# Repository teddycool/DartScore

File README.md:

# DartScore

DartScore is an open-source experiment in detecting darts with cameras and turning board hits into game scores. The repository contains a historical Python 3 single-camera MVP and a new, documented direction for a two-Pi system.

## Project status

- **Available now:** the original one-camera Pygame prototype, recorded test videos, a simple-score GameService, a durable camera-free simulator, an HTTP/SSE engine API, a web scoreboard/proxy, and optional boot-starting user services for the two Pis.
- **In design:** two-camera capture on a Raspberry Pi 5, 301/501 rules, browser kiosk startup, and status LEDs.
- **Accuracy:** the legacy detector is experimental. Replay candidate counts are a reproducible software baseline, not verified scoring accuracy.

The original MVP supports mounting and calibration states, one player, and a simple accumulating score. Its fixed 1680 × 1050 Pygame interface, hardcoded configuration and older camera dependencies have not been migrated to the new hardware. Do not treat the historical instructions as a current Pi 5 installation guide.

## Target architecture

The engine is deployed on a **Raspberry Pi 5 with 8 GB RAM** and a 512 GB M.2 SSD; two-camera capture is planned. A separate `GameService` applies game rules, owns game state, and persists accepted events. The engine exposes state, commands and events through a versioned HTTP/JSON API and server-sent events.

A **Raspberry Pi 4B with 2 GB RAM** serves the web UI and drives the screen. All player interaction happens in that browser; game rules and authoritative scores stay with the Pi 5. Both Pis use PoE and wired Ethernet. A display Pi restart does not reset a game.

For the initial web UI, the agreed controls are Start Game, Pause/Resume, and review of uncertain hits: confirm the proposed score, enter a correct single-dart score as points, or reject a false detection. Throws during Pause do not change game state and are not queued for Resume. Evidence images remain on the Pi 5 until manually deleted in the first version. Sector selection, 301/501 rules and automatic image cleanup are later implementation steps.

Read the design documents:

- [Current two-Pi implementation and round diagrams](Docs/current-implementation.md)
- [Two-Pi architecture and component migration](Docs/two-pi-architecture.md)
- [Engine/presentation API contract](Docs/engine-presentation-api-v1.md)
- [First web UI and uncertain-hit review](Docs/web-ui-first-release.md)

The architecture documents distinguish running components from planned camera and LED work.

## Simulate game input without cameras

The board-hit simulator exercises the extracted one-player game, uncertain-hit
review, Pause/Resume, and camera-health states without GPIO, Pygame, or video:

```sh
python3 SW/simulate_game.py Testdata/Simulations/basic_game.jsonl
python3 SW/simulate_game.py Testdata/Simulations/basic_game.jsonl --db runtime/game.sqlite3
python3 -m unittest discover -s tests -v
```

Each JSON Lines action produces a game snapshot and result. The example ends
with 80 points after a corrected hit; a throw during Pause is ignored. The
simulator is a developer tool. With `--db`, accepted actions, pending hits and
camera health recover after a process restart. Use a fresh database for a new
simulation scenario. See [the input contract](Docs/board-hit-input-and-simulator.md)
and [the persistence notes](Docs/durable-game-session.md).

## Deploy to two Pis for development

For iterative testing across two Pis, use
[the Python SSH/SFTP development deploy guide](Docs/two-pi-development-deploy.md).
It copies only the current engine code to the Pi 5 and presentation code to the
Pi 4B, keeping game data at its existing path, then restarts those processes.
Boot startup is available through optional per-user system services.
Use `--install-services` once after enabling user lingering on both Pis for
boot startup. For a shareable status/log report, run
`python3 deploy/collect_diagnostics.py`. See the deploy guide for details.

## Run the camera-free engine API

From the repository root, run `python3 SW/serve_engine.py --db runtime/game.sqlite3`.
It listens on loopback port 8765. State, health, commands and an SSE stream
are available for the existing `simple_score` game. Add `--dev-input` to
simulate board hits through a loopback-only development route. See
[the API contract and current scope](Docs/engine-presentation-api-v1.md).
Run `python3 SW/serve_presentation.py` in another terminal and open
`http://127.0.0.1:8080`. On the Pi 4B, set `--engine-url` to the Pi 5's
trusted-LAN address and use `--host 0.0.0.0` to serve its screen/browser.
See [web UI scope and setup](Docs/web-ui-first-release.md). The page
supports one-player simple score, Start, Pause/Resume, and pending-hit review;
it does not yet display stored evidence images.
For hands-on testing without cameras, use `python3 scripts/send_test_throw.py`
to submit one random dart (30% uncertain) and see
[the manual API command guide](Docs/manual-api-testing.md).

## Replay the legacy detector

The headless replay runs on a development computer without a camera, GPIO or Pygame. From the repository root, using Python 3.10 or later:

```sh
python3 -m venv .venv
.venv/bin/python -m pip install -r requirements-replay.txt
.venv/bin/python SW/replay_video.py Testdata/Videos/dartscore_20191107_152701.avi --output replay-report.json
```

The JSON report contains frame numbers, timestamps, candidate points and legacy scores. The first bundled video produced 238 frames and 9 candidates in the documented baseline run. Those scores are not ground truth: replay assumes the first frame is an empty board and does not automatically calibrate the video. See [the replay notes](Docs/video-replay-baseline.md) for the second video, options and limitations.

## Development path

1. Label recorded throws and verify board-hit/scoring behavior.
2. Integrate Pi 5 hardware status, two-camera capture and independent calibration.
3. Validate 301/501 rules and detection accuracy before treating scores as reliable.

Historical prototype setup instructions are retained in [Legacy single-camera setup (2020)](Docs/legacy-single-camera-setup.md). The original code layout is described in [the software notes](SW/README.md). The archived email `Docs/Re_ Method to Identify and Score Darts....eml` is kept for reference.

Licensed under [GNU GPLv3](LICENSE).

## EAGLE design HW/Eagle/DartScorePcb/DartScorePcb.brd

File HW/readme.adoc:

= Dartscore hardware

This readme file describes the DartScore hardware like board, cams, brackets, lightning, moutning details etc etc...

The board:
----------
I use a lightbox for the board to get even lighting conditions.
The 'frame' of the lightox is made of solid oak wood panels (from www.ess-enn.se) cut to the right size and with a
milled 'track'
for the led-tape (standard 12V with 5mm squared leds and c/c  15mm).
The led-strip is located at a distance of 70mm off, from the board-surface
and the inside of the box is 500x500 mm.

image:../Docs/dartboardlightbox.jpg[the lightingbox]

image:../Docs/20200106_105349.jpg[Closeup]

Closeup of the mounted led tape.

The Cam(s):
-----------
I use a raspberry pi 3 with a raspicam and the motioneyeos (https://github.com/ccrisan/motioneyeos)  in fast networked cam setup.
Currently one cam is used but the project will be prepared for two in the future.

image:Netcam_front.jpg[One of the netcams]

One of the cameras

image:../Docs/bracket-bottom.jpg[Camera bracket]

The 3d printed camera bracket. Cambracket 1/2.stl are the 3D printer models for this bracket.
I use standard M3 machine-screws to put it together.

In the future there will probably be a complete 3d printable enclosure with bracket for the cams, that fit is purpose
better then the one used today.

The PCB:
--------
In the 'eagle' directory is  a circuit board designed to use with a raspberry pi 4 as the
main computing device in the DartScore project.

The first version of the pcb is like an array of relays, designed with connectors for switches and leds and also for
the control of 2 fans,
one for the CPU and one for the 'box'.  In my project I use 'arcade-switches' from Adafruit and they need 5V as supply for
the builtin leds. Therefore all outputs are 'switched' with mosfets (the 'relays').
The same goes for the fans which are 12V
supplied (I use standard PC fans).

The PCB is available from here: https://aisler.net/p/PMFAHSJW

In the future the PCB will probably be more sofisticated, like one 12V inpout that drives everything including the
Pi itself.

image:DartScorePcb_v1.jpg[The pcb]

Physical installation:
----------------------

image:../Docs/20200105_154200.jpg[The PCB in action..]

Note that the PCB is mounted with the connectors on the ouside of the Pi-enclosure, otherwise the cooling-fan
shouldn't work. Th sockets to the left are used for connectiong the archade buttons and the socket to the right for
12V from a transformer, supplying the lightbox and the fans

The DartScore station:
----------------------
image:../Docs/20200105_185252.jpg[The station...]

The lightbox with the Adafruit archade switches mounted between the box and the screen.

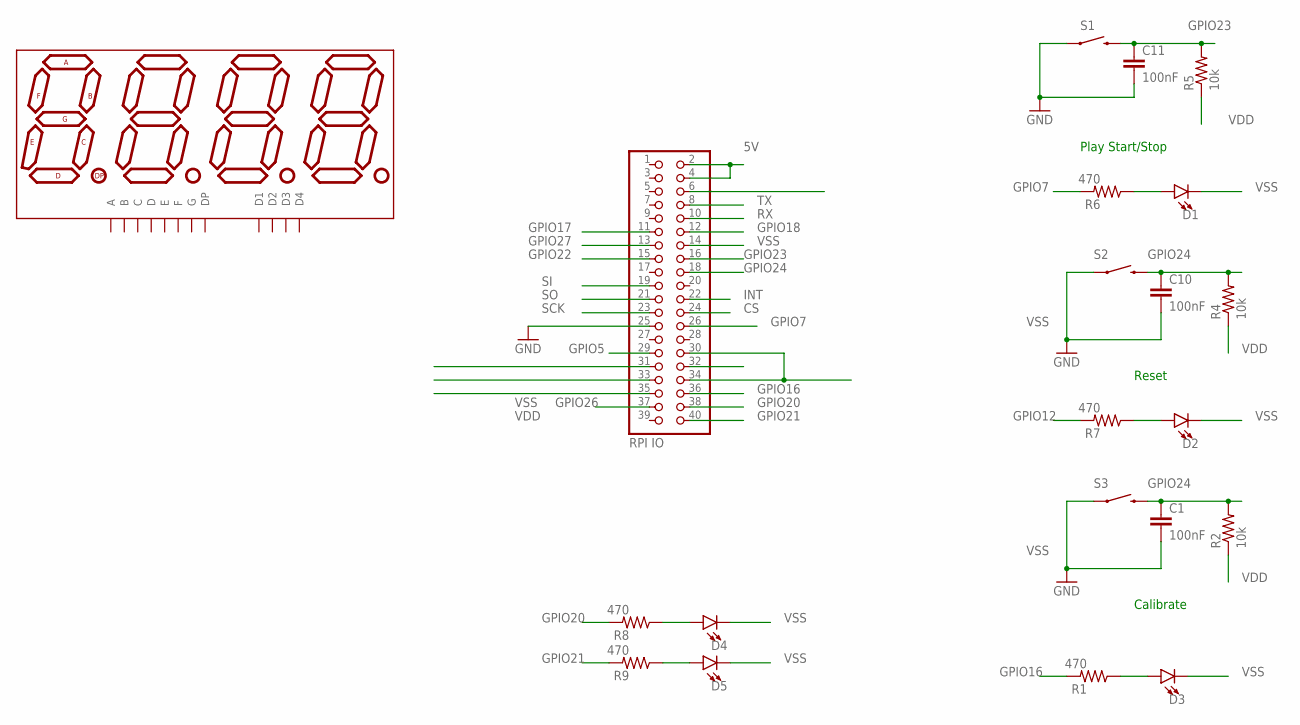
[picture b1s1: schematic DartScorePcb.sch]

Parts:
C1, C10, C11: 100nF; 0805
D1, D2, D3, D4, D5: LED3MM; LED_3MM
DISP1: ATA8041ARBJ; 7-SEGMENT-4DIGIT-20MM
JP2: RPI IO; 2X20
R1, R6, R7, R8, R9: 470; 0805
R2, R4, R5: 10k; 0805
S1, S2, S3: RESET; TACTILE-SWITCH-1101NE

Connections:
5V: JP2.2, JP2.4
CS: JP2.24
GPIO5: JP2.29
GPIO6: JP2.31
GPIO7: JP2.26, R6.2
GPIO12: JP2.32, R7.2
GPIO13: JP2.33
GPIO16: JP2.36, R1.2
GPIO17: JP2.11
GPIO18: JP2.12
GPIO19: JP2.35
GPIO20: JP2.38, R8.2
GPIO21: JP2.40, R9.2
GPIO22: JP2.15
GPIO23: C11.1, JP2.16, R5.2, S1.2
GPIO24: C1.1, C10.1, JP2.18, R2.2, R4.2, S2.2, S3.2
GPIO26: JP2.37
GPIO27: JP2.13
INT: JP2.22
unnamed: D3.A, R1.1
unnamed: D1.A, R6.1
unnamed: D2.A, R7.1
unnamed: D4.A, R8.1
unnamed: D5.A, R9.1
RX: JP2.10
SCK: JP2.23
SI: JP2.19
SO: JP2.21
TX: JP2.8
VDD: R2.1, R4.1, R5.1
VSS: C1.2, C10.2, C11.2, D1.K (C), D2.K (C), D3.K (C), D4.K (C), D5.K (C), JP2.6, JP2.14, JP2.25, JP2.30, JP2.34, S1.1, S2.1, S3.1

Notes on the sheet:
Play Start/Stop
Reset
Calibrate

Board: 2 copper layers, 21 parts (0 on the bottom side), 15 nets, no tracks yet.

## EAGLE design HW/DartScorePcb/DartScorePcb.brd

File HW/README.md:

# Dartscore hardware

Historical single-camera prototype hardware. The current two-Pi setup and
planned cameras are described in [the architecture](../Docs/two-pi-architecture.md).

## The board
I use a lightbox for the board to get even lighting conditions.
The 'frame' of the lightox is made of solid oak wood panels (from www.ess-enn.se) cut to the right size and with a
milled 'track'
for the led-tape (standard 12V with 5mm squared leds and c/c  15mm).
The led-strip is located at a distance of 70mm off, from the board-surface
and the inside of the box is 500x500 mm.

Closeup of the mounted led tape.

## The Cam(s)
I use a raspberry pi 3 with a raspicam and the motioneyeos (https://github.com/ccrisan/motioneyeos)  in fast networked cam setup.
Currently one cam is used but the project will be prepared for two in the future.

One of the cameras

The 3d printed camera bracket. Cambracket 1/2.stl are the 3D printer models for this bracket.
I use standard M3 machine-screws to put it together.

In the future there will probably be a complete 3d printable enclosure with bracket for the cams, that fit is purpose
better then the one used today.

## The PCB
In the 'eagle' directory is  a circuit board designed to use with a raspberry pi 4 as the
main computing device in the DartScore project.

The first version of the pcb is like an array of relays, designed with connectors for switches and leds and also for
the control of 2 fans,
one for the CPU and one for the 'box'.  In my project I use 'arcade-switches' from Adafruit and they need 5V as supply for
the builtin leds. Therefore all outputs are 'switched' with mosfets (the 'relays').
The same goes for the fans which are 12V
supplied (I use standard PC fans).

The PCB is available from here: https://aisler.net/p/PMFAHSJW

In the future the PCB will probably be more sofisticated, like one 12V inpout that drives everything including the
Pi itself.

## Physical installation

Note that the PCB is mounted with the connectors on the ouside of the Pi-enclosure, otherwise the cooling-fan
shouldn't work. Th sockets to the left are used for connectiong the archade buttons and the socket to the right for
12V from a transformer, supplying the lightbox and the fans

## The DartScore station

The lightbox with the Adafruit archade switches mounted between the box and the screen.

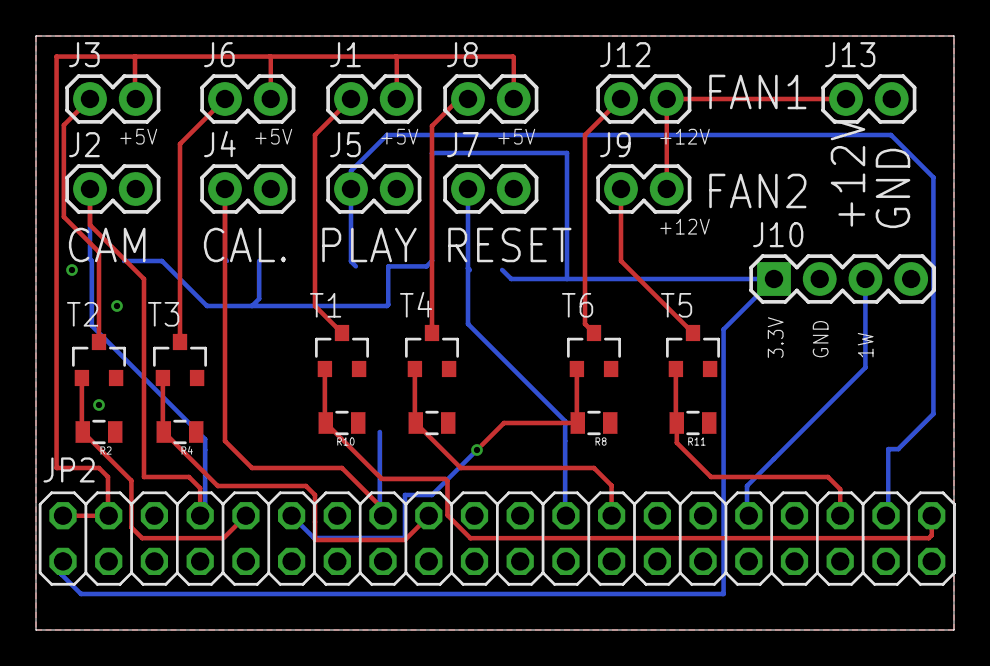
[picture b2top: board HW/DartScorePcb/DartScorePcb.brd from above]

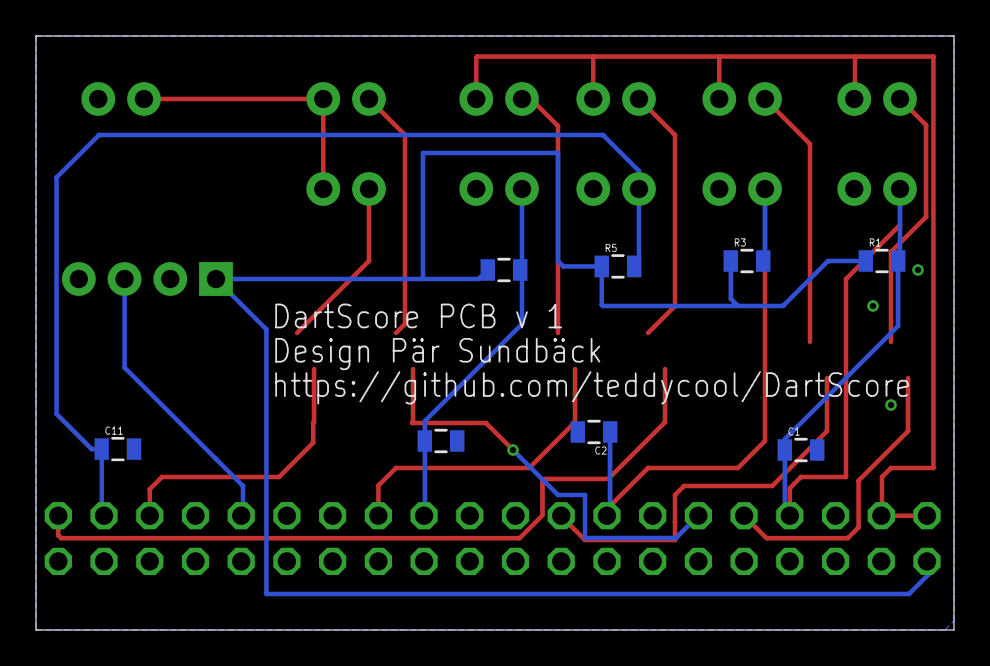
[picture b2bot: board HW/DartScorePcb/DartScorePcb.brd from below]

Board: 2 copper layers, 51.0 x 33.0 mm, 33 parts (8 on the bottom side), 21 nets.

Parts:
C1, C2, C3, C11: 100nF; 0805
J1: RESET_BUTTON_LIGHT; 1X02
J2: CAM_BUTTON_SWITCH; 1X02
J3: CAM_BUTTON_LIGHT; 1X02
J4: CAL_BUTTON_SWITCH; 1X02
J5: PLAY_BUTTON_SWITCH; 1X02
J6: CAL_BUTTON_LIGHT; 1X02
J7: RESET_BUTTON_SWITCH; 1X02
J8: PLAY_BUTTON_LIGHT; 1X02
J9: FAN_CONTROL; 1X02
J10: Sensors1; 1X04
J12, J13: CPU_FAN_CONTROL; 1X02
JP2: RPI IO; 2X20
R1, R2, R3, R4, R5, R6, R7, R8, R10, R11: 10k; 0805
T1, T2, T3, T4, T5, T6: BSS138; SOT23-3

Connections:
5V: J1.2, J3.2, J6.2, J8.2, JP2.2, JP2.4
12V: J9.2, J12.2, J13.1
GPIO7: JP2.26, R7.2, T4.1
GPIO8: C3.1, J7.1, JP2.24, R6.2
GPIO12: J10.3, JP2.32
GPIO14: C1.1, J2.1, JP2.8, R1.2
GPIO15: JP2.10, R2.2, T2.1
GPIO16: JP2.36, R11.2, T5.1
GPIO18: JP2.12, R8.2, T6.1
GPIO20: C11.1, J5.1, JP2.38, R5.2
GPIO21: JP2.40, R10.2, T1.1
GPIO23: C2.1, J4.1, JP2.16, R3.2
GPIO24: JP2.18, R4.2, T3.1
unnamed: J9.1, T5.3
unnamed: J1.1, T1.3
unnamed: J12.1, T6.3
unnamed: J3.1, T2.3
unnamed: J6.1, T3.3
unnamed: J8.1, T4.3
VDD: J10.1, JP2.1, R1.1, R3.1, R5.1, R6.1
VSS: C1.2, C2.2, C3.2, C11.2, J2.2, J4.2, J5.2, J7.2, J10.2, J13.2, JP2.6, JP2.14, JP2.20, JP2.25, JP2.39, R2.1, R4.1, R7.1, R8.1, R10.1, R11.1, T1.2, T2.2, T3.2, T4.2, T5.2, T6.2

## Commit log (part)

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2015-06-08 no message
2015-06-08 test
2015-06-15 DartScore stup part 2...
2015-06-20 New testimages and new state-handling. Moving logic to state-classes.
2015-06-25 New structure, still not complete and working..
2015-06-25 Start of config
2015-09-27 Start of new bransch
2015-11-07 Some fixes but still not running...
2015-11-09 Removed a lot of junk that isn't used in this approach. State-loops, vision and board are main-components now. Added some support for image-writing to mjpeg-streamer directly from opencv.
2015-11-09 Start of working StateLoops
2015-11-12 Working playstate and dart recognition
2015-11-14 More cleanup and removing things not used. Added examples from videostream.
2015-11-14 More on states. Added support pushbuttons and code for two, cal and game. Added a logger but no code for this yet.
2015-11-26 small fixes and more frame-examples with matching cam and cv frames.
2015-12-15 Better performance with python generator for image-stream and lower resolution.
2016-03-06 Cleaned up and moved around some things. Starting some work with calibration of board and finding sectors.
2016-07-06 Cleaned up and moved around some more things. Added LED indicators and a switch. More use of config...
2017-03-26 Added a Recorder-module and also a small testprogram record.py to record a videofile with the componentes in the project that can be used for testing. Also provided an example of such a file.
2017-03-27 Added Videos-dir and two videofiles. The exact same dartrounds in two versions. 1: (raw) directly from cam 2:(cv) from opencv with findings and statustexts etc Vision module now updated allways recor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
2017-04-01 Description and states added in a first version
2017-04-03 Sound and Video File
    Added a Test video of my current setup
    Added Sound Files for possilbe audio output of Russ Bray
2017-04-03 Separated cam (frame-generation) from vision. Two cam-classes, one for pi and one for pc. Both returning a frame. Which cam to use is set in DartScoreConfig.
2017-04-03 Removed dependencies to gpio
2017-04-03 Removed dependencies to gpio Created Documentation folder for documents
2017-04-04 Added system query for debugging purpose + image frame of different setup
2017-04-05 New bransch and reworked repo
2017-04-05 Clean up
2017-04-05 New readme...
2017-04-05 Added directorry for WinSetup
2017-04-08 First attemt to separate different environment with the same statemachine. Cam and presenter is working but not the actual DartScoreEngine. That's the next step..
2017-04-09 Everthing runs through the state-machine but still the actual states are not fully implemented.
2017-04-09 Started to implement calibration in Board2.py using different video-files as test-material.
2017-04-26 Added super-simple first version of a frontend with PyGame. This will be the main presenter in my project. Now thr video-feed is 'mirrored' but the screen and surface blits are working
2019-11-03 First commit of new bransh
    Forked from 'DartScoreEngine' and setup for networked cams. Engine ported to Python3 (allmost) but this is a work in progress and far from finished...
2019-11-03 Update
    Cleaned up and with a working 'recorder' and some video files for testing.
2019-11-09 Changed project structure
2019-11-20 Work in progress
    A lot of changes and a small step forward...
    New and updated documents and test-videos. Partly new file structure.
2019-11-20 removed idea
2019-11-30 Working pieces
    A lot of pieces are now working by themselves but a lot of work remains for the integration of everything.
2019-12-15 MVP1
    This is the minimum viable product of DartScore!!
    It works and calculate correct scores in > 80% of the cases
2019-12-15 Create LICENSE
2019-12-15 Image fix
2019-12-24 Small updates of docs..
    Updated readmes
    Removed the mp4 files that will evenually move to youtube
2020-01-06 Documentation...
    Mostly update of documentation but also some small code-changes.

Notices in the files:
parts and their libraries:
SparkFun-Passives: Licensing: Creative Commons ShareAlike 4.0 International - https://creativecommons.org/licenses/by-sa/4.0
